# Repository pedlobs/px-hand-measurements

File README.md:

# PX Hand Measurements

PX Hand Measurements is a prototype for acquiring hand sensor data. The repository currently contains STM32 firmware, an incomplete Python desktop application, KiCad board-design files, and a NestJS starter project.

> **Current status:** the firmware and Python application are not yet integrated into a working end-to-end workflow. In particular, the firmware's serial output format is not accepted by the Python serial parser, and the desktop application's UI and some referenced types/configuration are incomplete.

## Overview

The diagram below shows the intended measurement flow and the current implementation boundary. Solid arrows indicate data the firmware emits; dashed arrows are the intended host-app path, which is not yet functional end to end.

```text
Sensors / analog circuit
          |
          v
STM32WB55 firmware
  ADC: C0-C3; PWM outputs
          |
          | USB CDC: "C0=... C1=... C2=... C3=..."
          v
      USB serial
          |
          | - - - format mismatch: SerialWorker does not parse C0=... lines
          v
host_app / SerialWorker - - -> telemetry queue - - -> Tkinter UI [incomplete]
                                                       |
                                                       | intended capture
                                                       v
                                                 DataLogger
                                                       |
                                                       | .xlsx
                                                       v
                                                 DataMerger
                                                       |
                                                       v
                                               consolidated .csv

hardware/kicad_project: schematic and PCB for the electronics
hardware/freecad: mechanical prototype macro
API-Testing--main: NestJS starter configuration, not an implemented API
```

The host application's serial, UI, logging, and consolidation pieces are not currently integrated into a working workflow.

## Repository structure

| Path | Contents |
| --- | --- |
| `4_sensors_4_led_working/UART_Example/` | STM32CubeIDE/CubeMX project for the STM32WB55 |
| `4_sensors_4_led_working/UART_Example/Core/Src/main.c` | ADC acquisition, USB CDC output, and PWM updates |
| `4_sensors_4_led_working/UART_Example/UART_Example.ioc` | STM32CubeMX peripheral and pin configuration |
| `host_app/src/main.py` | Python desktop application entry point using Tkinter |
| `host_app/src/config.py` | Serial, hardware, and UI configuration dataclasses |
| `host_app/src/models/telemetry.py` | Telemetry data model |
| `host_app/src/services/serial_worker.py` | Serial-port reading, parsing, and simulated telemetry |
| `host_app/src/services/data_logger.py` | Excel capture service |
| `host_app/src/services/data_merger.py` | Excel-to-CSV consolidation service |
| `host_app/requirements.txt` | Python dependency file; currently empty |
| `hardware/kicad_project/` | KiCad schematic, PCB layout, and project |
| `hardware/freecad/px_hand_fixture.FCMacro` | FreeCAD macro for a provisional mechanical fixture model |
| `hardware/kicad_project/pcb projet-backups/` | KiCad board backups |
| `API-Testing--main/API-Testing--main/` | NestJS project configuration; no application source is currently present |

Generated STM32 build files are under `4_sensors_4_led_working/UART_Example/Debug/`. Treat them as build outputs rather than the primary source to edit.

## STM32 firmware

The firmware project targets the **STM32WB55RGVx** and is configured for STM32CubeWB **V1.23.0**. Its `.ioc` file configures ADC1 for four conversions:

| Firmware label | MCU pin | ADC channel |
| --- | --- | --- |
| `C0` | `PC0` | 1 |
| `C1` | `PC1` | 2 |
| `C2` | `PA0` | 5 |
| `C3` | `PA1` | 6 |

The firmware sends one text line over USB CDC approximately every 200 ms, for example:

```text
C0=2345  C1=2301  C2=2198  C3=2450
```

It also updates four PWM channels from the ADC readings. The output pins and peripheral configuration are recorded in `UART_Example.ioc`.

### Build and flash

1. Install **STM32CubeIDE** and the matching STM32WB firmware package.
2. Open `4_sensors_4_led_working/UART_Example/` as an existing STM32CubeIDE project.
3. Check the target and build settings, then build in the IDE.
4. Connect the board and flash it using the procedure for your board and programmer.

The checked-in `Debug` build files may include environment-specific settings. Use STM32CubeIDE to regenerate or configure the build for your machine rather than assuming the generated makefile is portable.

## Python desktop application

The Python application is under `host_app/` and is structured as a Tkinter desktop app with serial and data services. Its current source includes:

- Serial port enumeration and reading at a configurable baud rate (default `115200`).
- A parser for JSON telemetry (`s`/`sensors` and optional `l`/`leds` fields) and whitespace-separated numeric readings.
- A simulation mode that generates four sensor and four LED values.
- Services intended to save capture samples to `.xlsx` and consolidate spreadsheets into a semicolon-separated CSV.

The data logger's legacy spreadsheet columns are:

```text
Timestamp, Name, DOB, Age, Description, Movement, Finger, C0, C1, C2, C3
```

The merger groups records by movement and finger. It uses `C3` for `Push` and `Pull`; for other movement values it calculates statistics for `C0`, `C1`, and `C2`.

### Current implementation gaps

The desktop application is **not currently runnable as a complete application**:

- `host_app/src/ui/app_window.py` is empty, although `main.py` imports `PxHandAppWindow` from it.
- The logger and merger import `LoggingConfig`, which is not defined in `host_app/src/config.py`.
- The logger imports `TrialMetadata`, which is not defined in `host_app/src/models/telemetry.py`.
- `host_app/requirements.txt` is empty, although the services import third-party packages such as `pyserial`, `openpyxl`, and `pandas`.
- The firmware emits labeled values such as `C0=2345`, but `SerialWorker` currently parses JSON or whitespace-separated numbers. The firmware's current output therefore will not be parsed by that worker.

These items need to be resolved before documenting a supported run command or end-to-end data-capture workflow. The app code should be treated as an incomplete prototype, not a released workflow.

## KiCad board design

The KiCad project files are in `hardware/kicad_project/`:

- `pcb projet.kicad_pro` - project settings
- `pcb projet.kicad_sch` - schematic
- `pcb projet.kicad_pcb` - PCB layout

Open the `.kicad_pro` file in KiCad to inspect the schematic and board together. Check the component pin assignments, power, connectors, and consistency with the firmware before manufacturing or changing the hardware.

## FreeCAD mechanical prototype

`hardware/freecad/px_hand_fixture.FCMacro` generates a concept model in FreeCAD. Opening the `.FCMacro` with **File > Open** shows its code in the macro editor; it does not run it. With the macro open in the editor, use the **Execute macro** button (play icon) to run it. The macro creates a new document; use **Save As** to save the resulting model as `.FCStd`. Alternatively, install the macro in FreeCAD's configured macro directory and run it from **Macro > Macros**.

The current provisional model includes:

- A base approximately `101.25 x 122.53 x 8 mm`, with a 12 x 8 staggered triangular pattern of through-holes.
- Hole diameter `2.5 mm`, clear gap between hole edges `8 mm`, and `10 mm` margin from the outer holes to the base edge.
- One side wall approximately `90 x 20 x 4 mm`, aligned with an interior row of the base so all four modeled fingers are supported.
- Three separate sensor-carriage groups that can be repositioned along the finger-length axis. Each has an `8 x 8 x 4 mm` sensor placeholder (reduced 20% from the previous placeholder), illustrative rollers, and a lock-knob placeholder.
- Four isolated finger references (no palm or thumb), with the index finger against the sensors and the middle finger on the opposite side of the wall. Each finger has cylindrical phalanges and smaller colored markers at its DIP, PIP, and MCP joints.

The 90 mm wall and rails provide travel for the longest modeled finger (82 mm); the three carriages start at 20%, 50%, and 80% of the rail, near the three phalange regions. Sensor dimensions are still placeholders because the physical sensor has not been selected. Joint locations and finger lengths are schematic proportions for visualization. The orange spheres mark the distal interphalangeal (DIP), proximal interphalangeal (PIP), and metacarpophalangeal (MCP) joints; they do not represent fingernails. The model is not a fit or anatomical validation.

The macro's dimensions are constants near the top of the file. The generated solids are a visual prototype, not a fully constrained mechanism: carriage travel, roller clearances, locking force, wall attachment, and print tolerances still require design review and physical testing. Edit the macro parameters and rerun it to generate a revised document.

## NestJS starter project

`API-Testing--main/API-Testing--main/` contains NestJS configuration and package manifests, but no `src/` or test directory is present in the current repository tree. It is not currently an implemented measurement API.

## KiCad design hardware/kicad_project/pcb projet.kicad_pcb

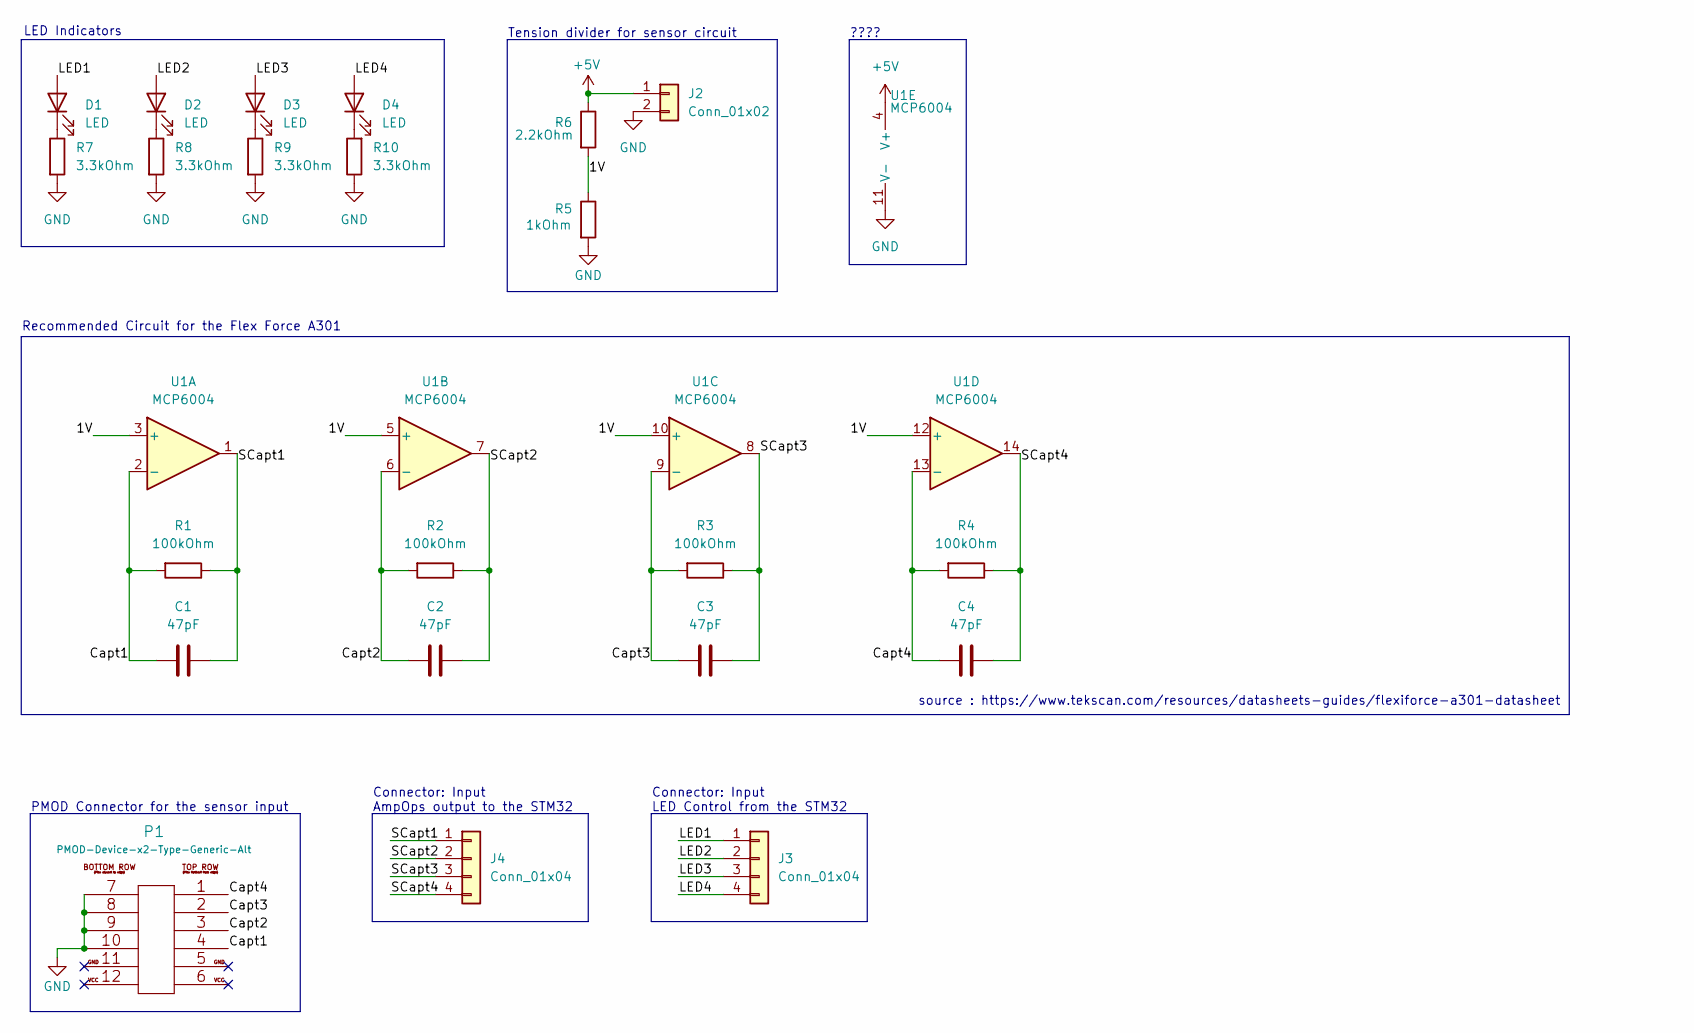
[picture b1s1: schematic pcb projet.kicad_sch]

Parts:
C1, C2, C3, C4: 47pF; C_Axial_L3.8mm_D2.6mm_P7.50mm_Horizontal
D1, D2, D3, D4: LED; LED_D5.0mm
J2: Conn_01x02; PinHeader_1x02_P2.54mm_Vertical
J3, J4: Conn_01x04; PinHeader_1x04_P2.54mm_Vertical
P1: PMOD-Device-x2-Type-Generic-Alt; pmod_pin_array_6x2
R1, R2, R3, R4: 100kOhm; R_Axial_DIN0207_L6.3mm_D2.5mm_P7.62mm_Horizontal
R5: 1kOhm; R_Axial_DIN0207_L6.3mm_D2.5mm_P7.62mm_Horizontal
R6: 2.2kOhm; R_Axial_DIN0207_L6.3mm_D2.5mm_P7.62mm_Horizontal
R7, R8, R9, R10: 3.3kOhm; R_Axial_DIN0207_L6.3mm_D2.5mm_P7.62mm_Horizontal
U1: MCP6004; DIP-14_W7.62mm_LongPads

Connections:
+5V: J2.1, R6.1, U1.4 (V+)
/1V: R5.1, R6.2, U1.3 (+), U1.5 (+), U1.10 (+), U1.12 (+)
/Capt1: C1.2, P1.4, R1.2, U1.2 (-)
/Capt2: C2.2, P1.3, R2.2, U1.6 (-)
/Capt3: C3.2, P1.2, R3.2, U1.9 (-)
/Capt4: C4.2, P1.1, R4.2, U1.13 (-)
/LED1: D1.2 (A), J3.1
/LED2: D2.2 (A), J3.2
/LED3: D3.2 (A), J3.3
/LED4: D4.2 (A), J3.4
/SCapt1: C1.1, J4.1, R1.1, U1.1
/SCapt2: C2.1, J4.2, R2.1, U1.7
/SCapt3: C3.1, J4.3, R3.1, U1.8
/SCapt4: C4.1, J4.4, R4.1, U1.14
GND: J2.2, P1.7, P1.8, P1.9, P1.10, R5.2, R7.2, R8.2, R9.2, R10.1, U1.11 (V-)
unnamed: D1.1 (K), R7.1
unnamed: D2.1 (K), R8.1
unnamed: D3.1 (K), R9.1
unnamed: D4.1 (K), R10.2

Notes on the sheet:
LED Indicators
Connector: Input LED Control from the STM32
source : https://www.tekscan.com/resources/datasheets-guides/flexiforce-a301-datasheet
PMOD Connector for the sensor input
Connector: Input AmpOps output to the STM32
Recommended Circuit for the Flex Force A301
Tension divider for sensor circuit
????

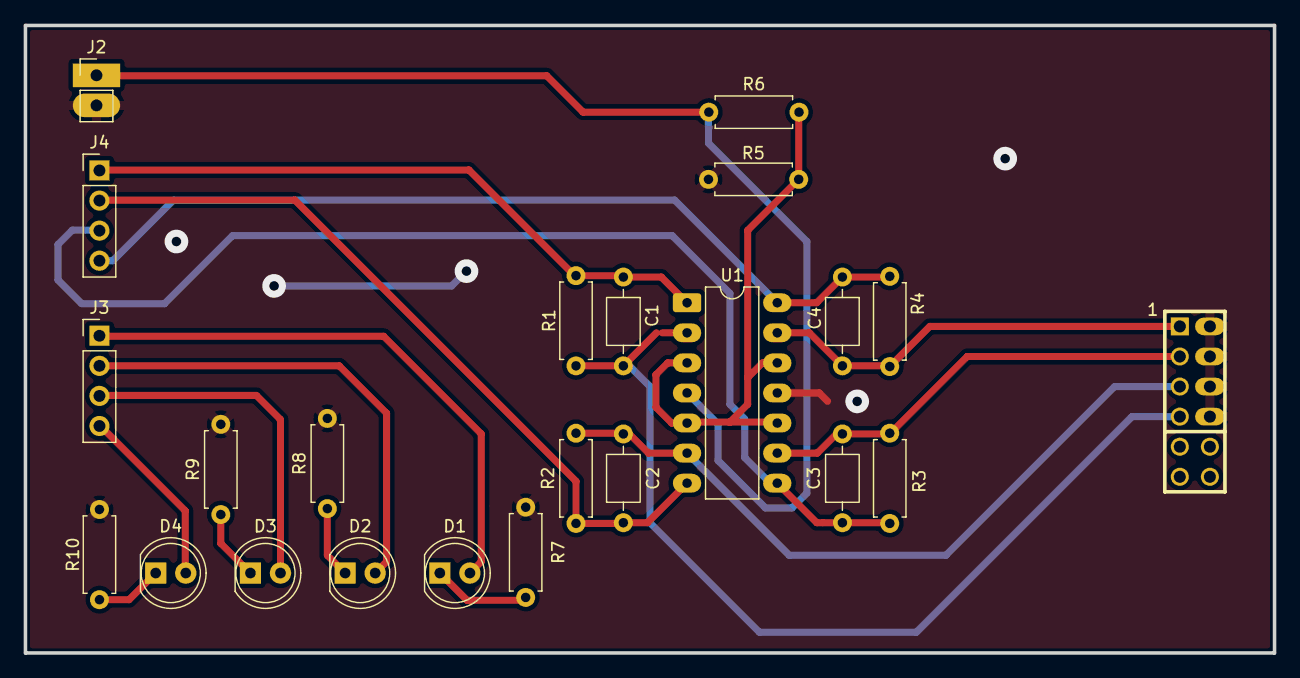
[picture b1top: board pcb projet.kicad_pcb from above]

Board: 2 copper layers, 105.5 x 53.0 mm, 23 parts (1 on the bottom side), 19 nets.

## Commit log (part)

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2026-01-23 add merging files
2026-01-23 add python code
2026-01-23 add pcb and stm files
